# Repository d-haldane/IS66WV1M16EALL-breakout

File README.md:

# IS66WV1M16EALL-breakout

Breakout a flash chip for Mats

It's a S66WV1M16EBLL-70BLI (https://mouser.se/datasheet/2/198/66WV1M16EALL_EBLL-1077555.pdf). Is it possible to break out a 0.75mm pitch BGA within the specs of, for instance, JLC? Their filled&capped via-in-pad service on 6/8L have a super deal now for 50x50mm boards with 0.3mm drills. Just $5 instead of $50.

Thanks. I have no real requirements in regards of pin ordering, nor the connectors. I guess that 50mil pinheaders would make a usable small interface. If they're kept as single row the board could easily be respun as reasonably small castellated board.

GPT4 did the pinout of the chip - but I can't share chats with images. Lame.

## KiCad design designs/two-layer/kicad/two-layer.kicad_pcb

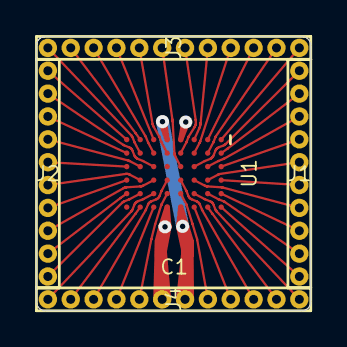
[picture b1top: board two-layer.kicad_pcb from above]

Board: 2 copper layers, 15.2 x 15.2 mm, 6 parts (0 on the bottom side), 44 nets.

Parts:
C1: 22u; Pkg0603
J1, J2: PIN_GRID_1
J3, J4: PIN_GRID
U1: LP_MY_COMPONENT

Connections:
escape0_p: J1.1, U1.C3
escape1_p: J1.2, U1.A2
escape2_p: J1.3, U1.B3
escape3_p: J1.4, U1.A3
escape4_p: J1.5, U1.B4
escape5_p: J1.6, U1.A4
escape6_p: J1.7, U1.C4
escape7_p: J1.8, U1.A5
escape8_p: J1.9, U1.B5
escape9_p: J1.10, U1.A6
escape10_p: J2.1, U1.H1
escape11_p: J2.2, U1.F3
escape12_p: J2.3, U1.H2
escape13_p: J2.4, U1.G3
escape14_p: J2.5, U1.H3
escape15_p: J2.6, U1.G4
escape16_p: J2.7, U1.H4
escape17_p: J2.8, U1.F4
escape18_p: J2.9, U1.H5
escape19_p: J2.10, U1.G5
escape20_p: J3.1, U1.G2
escape21_p: J3.2, U1.G1
escape22_p: J3.3, U1.F2
escape23_p: J3.4, U1.F1
escape24_p: J3.5, U1.E2
escape25_p: J3.6, U1.D3
escape26_p: J3.7, U1.D2
escape27_p: J3.8, U1.C1
escape28_p: J3.9, U1.C2
escape29_p: J3.10, U1.B1
escape30_p: J3.11, U1.B2
escape31_p: J3.12, U1.A1
escape32_p: J4.1, U1.F5
escape33_p: J4.2, U1.G6
escape34_p: J4.3, U1.E4
escape35_p: J4.4, U1.F6
escape36_p: J4.5, U1.E5
escape38_p: C1.1, J4.7, U1.D6, U1.E1
escape39_p: J4.8, U1.D5
escape40_p: J4.9, U1.C6
escape41_p: J4.10, U1.D4
escape42_p: J4.11, U1.B6
escape43_p: J4.12, U1.C5
gnd: C1.2, J4.6, U1.D1, U1.E6

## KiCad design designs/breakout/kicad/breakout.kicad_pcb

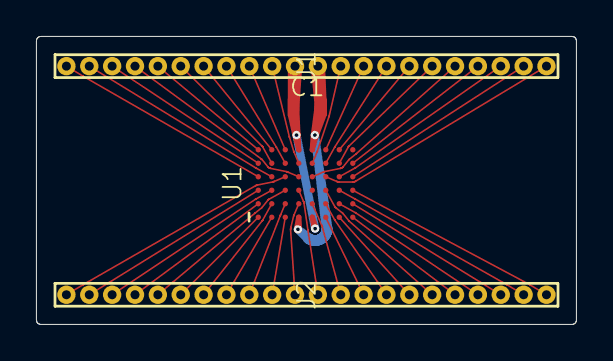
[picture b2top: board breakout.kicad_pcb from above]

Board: 4 copper layers, 30.0 x 16.0 mm, 4 parts (0 on the bottom side), 44 nets.

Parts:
C1: 22u; Pkg0603
J1, J2: PIN_GRID
U1: LP_MY_COMPONENT

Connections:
escape0_p: J1.1, U1.A4
escape1_p: J1.2, U1.B4
escape2_p: J1.3, U1.A5
escape3_p: J1.4, U1.D4
escape4_p: J1.5, U1.A6
escape5_p: J1.6, U1.B5
escape6_p: J1.7, U1.B6
escape7_p: J1.8, U1.C5
escape8_p: J1.9, U1.C6
escape9_p: J1.10, U1.D5
escape10_p: C1.1, J1.11, U1.D6, U1.E1
escape11_p: C1.2, J1.12, U1.D1, U1.E6
escape12_p: J1.13, U1.E5
escape13_p: J1.14, U1.F6
escape14_p: J1.15, U1.F5
escape15_p: J1.16, U1.G6
escape16_p: J1.17, U1.G5
escape17_p: J1.18, U1.E4
escape18_p: J1.19, U1.H5
escape19_p: J1.20, U1.G4
escape20_p: J1.21, U1.H4
escape21_p: J1.22, U1.F4
escape22_p: J2.1, U1.C4
escape23_p: J2.2, U1.A3
escape24_p: J2.3, U1.B3
escape25_p: J2.4, U1.A2
escape26_p: J2.5, U1.C3
escape27_p: J2.6, U1.A1
escape28_p: J2.7, U1.B2
escape29_p: J2.8, U1.B1
escape30_p: J2.9, U1.C2
escape31_p: J2.10, U1.C1
escape32_p: J2.11, U1.D2
escape33_p: J2.12, U1.D3
escape34_p: J2.13, U1.E2
escape35_p: J2.14, U1.F1
escape36_p: J2.15, U1.F2
escape37_p: J2.16, U1.G1
escape38_p: J2.17, U1.F3
escape39_p: J2.18, U1.H1
escape40_p: J2.19, U1.G2
escape41_p: J2.20, U1.H2
escape42_p: J2.21, U1.G3
escape43_p: J2.22, U1.H3

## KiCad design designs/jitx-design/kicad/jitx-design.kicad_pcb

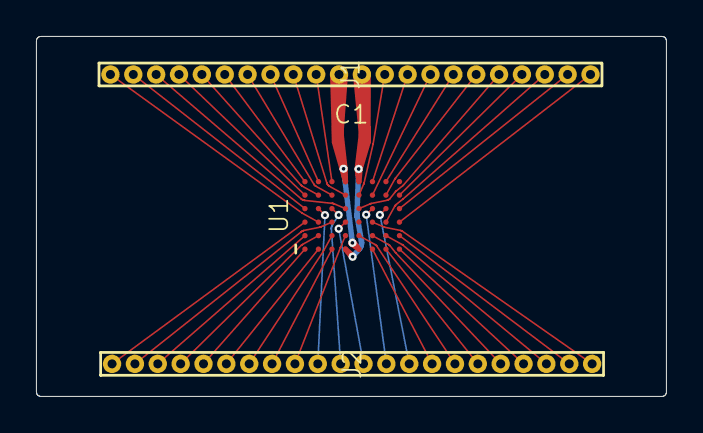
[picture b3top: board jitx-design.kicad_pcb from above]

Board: 4 copper layers, 35.0 x 20.0 mm, 4 parts (0 on the bottom side), 44 nets.

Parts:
C1: 22u; Pkg0603
J1, J2: PIN_GRID
U1: LP_MY_COMPONENT

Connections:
escape0_p: J1.1, U1.H3
escape1_p: J1.2, U1.H4
escape2_p: J1.3, U1.G3
escape3_p: J1.4, U1.H5
escape4_p: J1.5, U1.E4
escape5_p: J1.6, U1.G5
escape6_p: J1.7, U1.G6
escape7_p: J1.8, U1.F5
escape8_p: J1.9, U1.F6
escape9_p: J1.10, U1.E5
escape10_p: C1.2, J1.11, U1.D1, U1.E6
escape11_p: C1.1, J1.12, U1.D6, U1.E1
escape12_p: J1.13, U1.C6
escape13_p: J1.14, U1.D5
escape14_p: J1.15, U1.B6
escape15_p: J1.16, U1.C5
escape16_p: J1.17, U1.A6
escape17_p: J1.18, U1.B5
escape18_p: J1.19, U1.A5
escape19_p: J1.20, U1.D4
escape20_p: J1.21, U1.A4
escape21_p: J1.22, U1.B3
escape22_p: J2.1, U1.F3
escape23_p: J2.2, U1.H2
escape24_p: J2.3, U1.G2
escape25_p: J2.4, U1.H1
escape26_p: J2.5, U1.F2
escape27_p: J2.6, U1.G1
escape28_p: J2.7, U1.E2
escape29_p: J2.8, U1.F1
escape30_p: J2.9, U1.G4
escape31_p: J2.10, U1.F4
escape32_p: J2.11, U1.D3
escape33_p: J2.12, U1.C4
escape34_p: J2.13, U1.B4
escape35_p: J2.14, U1.D2
escape36_p: J2.15, U1.C1
escape37_p: J2.16, U1.C2
escape38_p: J2.17, U1.B1
escape39_p: J2.18, U1.A1
escape40_p: J2.19, U1.B2
escape41_p: J2.20, U1.A2
escape42_p: J2.21, U1.C3
escape43_p: J2.22, U1.A3

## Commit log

2023-10-14 routing design
2023-10-14 Routed V0
2023-10-14 Generate Kicad
2023-10-14 single layer io version
2023-10-14 Add new kicad
2023-10-14 Key L596/D302 does not exist in table.
2023-10-16 Export two layer version
